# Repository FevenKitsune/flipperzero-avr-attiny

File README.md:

# flipperzero-avr-attiny
Small external module for the Flipper Zero to socket ATtiny84's and 85's. Also includes an ICSP header.

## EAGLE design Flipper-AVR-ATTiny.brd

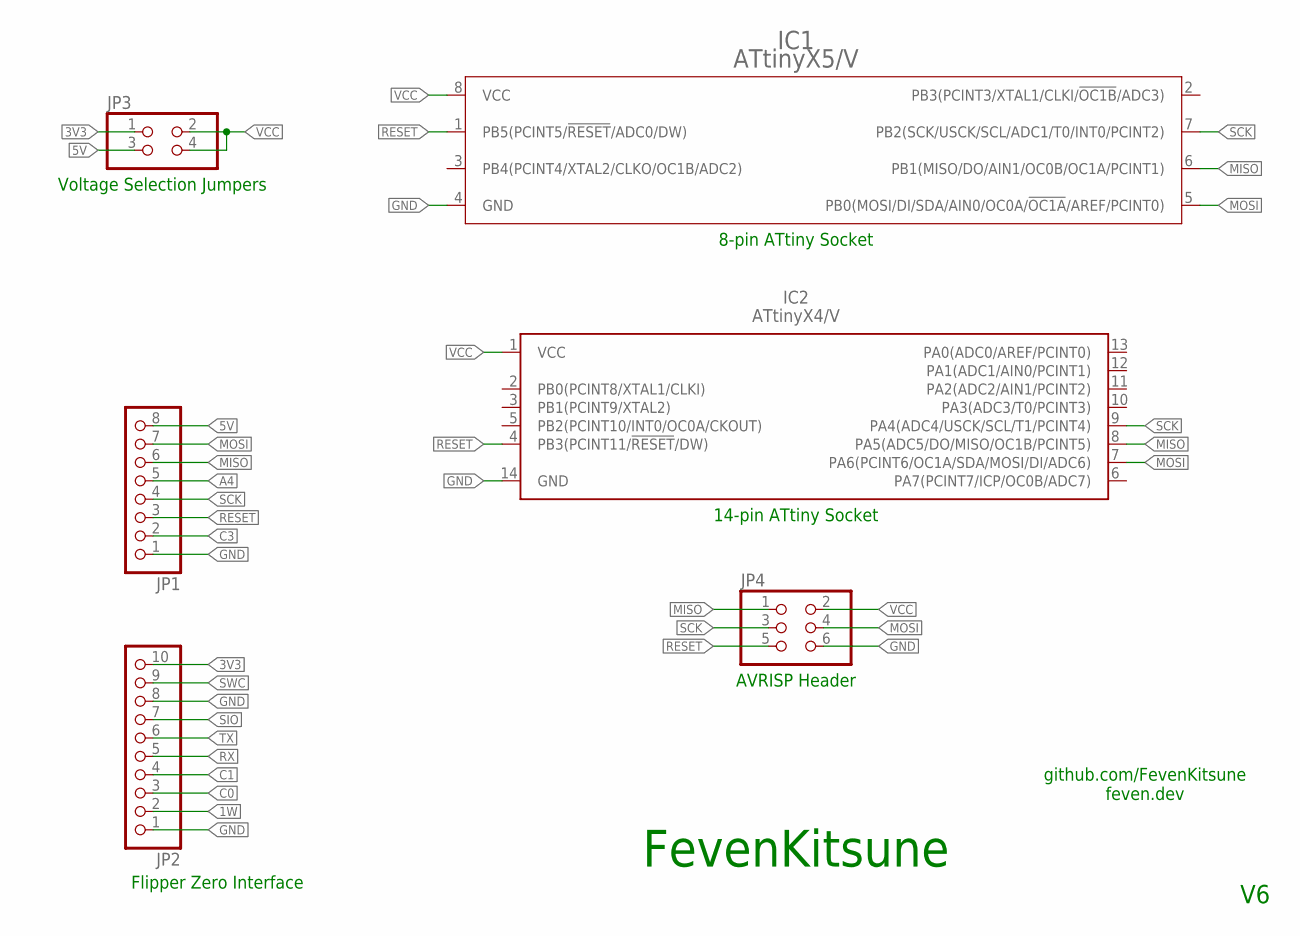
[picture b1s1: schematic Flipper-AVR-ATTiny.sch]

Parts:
IC1: ATtinyX5/V; DIP787W55P254L958H533Q8B-8P3
IC2: ATtinyX4/V; DIP762W55P254L1917H533Q14B
JP1: PINHD-1X8; 1X08
JP2: PINHD-1X10; 1X10
JP3: PINHD-2X2; 2X02
JP4: PINHD-2X3; 2X03

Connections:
1W: JP2.2
3V3: JP2.10, JP3.1
5V: JP1.8, JP3.3
A4: JP1.5
C0: JP2.3
C1: JP2.4
C3: JP1.2
GND: IC1.4 (GND), IC2.14 (GND), JP1.1, JP2.1, JP2.8, JP4.6
MISO: IC1.6 (PB1(MISO/DO/AIN1/OC0B/OC1A/PCINT1)), IC2.8 (PA5(ADC5/DO/MISO/OC1B/PCINT5)), JP1.6, JP4.1
MOSI: IC1.5 (PB0(MOSI/DI/SDA/AIN0/OC0A/!OC1A!/AREF/P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), IC2.7 (PA6(PCINT6/OC1A/SDA/MOSI/DI/ADC6)), JP1.7, JP4.4
RESET: IC1.1 (PB5(PCINT5/!RESET!/ADC0/DW)), IC2.4 (PB3(PCINT11/!RESET!/DW)), JP1.3, JP4.5
RX: JP2.5
SCK: IC1.7 (PB2(SCK/USCK/SCL/ADC1/T0/INT0/PCINT2)), IC2.9 (PA4(ADC4/USCK/SCL/T1/PCINT4)), JP1.4, JP4.3
SIO: JP2.7
SWC: JP2.9
TX: JP2.6
VCC: IC1.8 (VCC), IC2.1 (VCC), JP3.2, JP3.4, JP4.2

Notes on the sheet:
Voltage Selection Jumpers
AVRISP Header
14-pin ATtiny Socket
8-pin ATtiny Socket
Flipper Zero Interface
FevenKitsune
github.com/FevenKitsune feven.dev

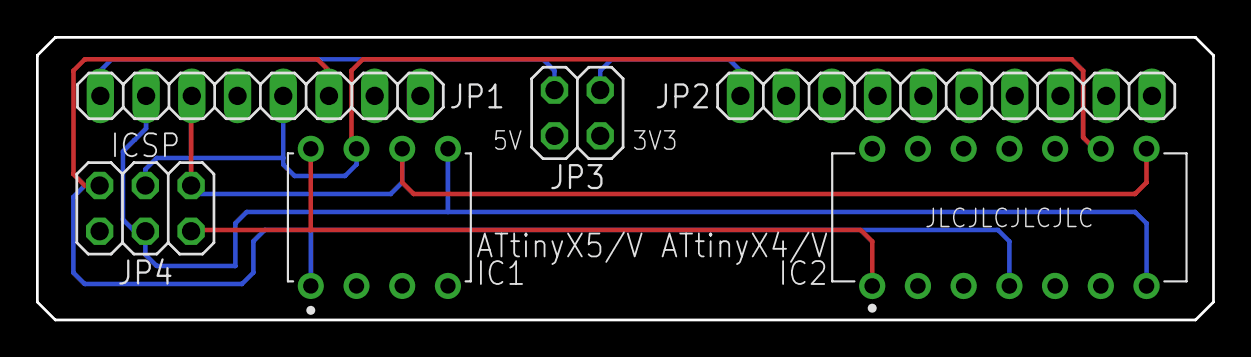
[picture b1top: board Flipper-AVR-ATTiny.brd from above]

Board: 2 copper layers, 65.3 x 15.7 mm, 6 parts (0 on the bottom side), 8 nets.

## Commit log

2023-05-12 Added images!
